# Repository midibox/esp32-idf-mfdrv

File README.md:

# MBHP_MF_NG for ESP32

## Introduction

This application is originated from the PIC based MBHP_MF_NG project: http://www.ucapps.de/mbhp_mf_ng.html

Currently used as a "Proof of Concept" for ESP32 based motorfader control.

Advantage: due to the dedicated PWM outputs of ESP32 we get much more accurate control over the motors.

More documentation to follow...

## Important

Please optimize the app configuration with "idf.py menuconfig":

* Compiler Options->Optimization Level: set to -Os (Release)
* Component Config->ESP32 Specific: set Minimum Supported ESP32 Revision to 1 (if you have a newer device...)
* Component Config->ESP32 Specific: set CPU frequency to 240 MHz
* Component Config->FreeRTOS: set Tick rate (Hz) to 1000

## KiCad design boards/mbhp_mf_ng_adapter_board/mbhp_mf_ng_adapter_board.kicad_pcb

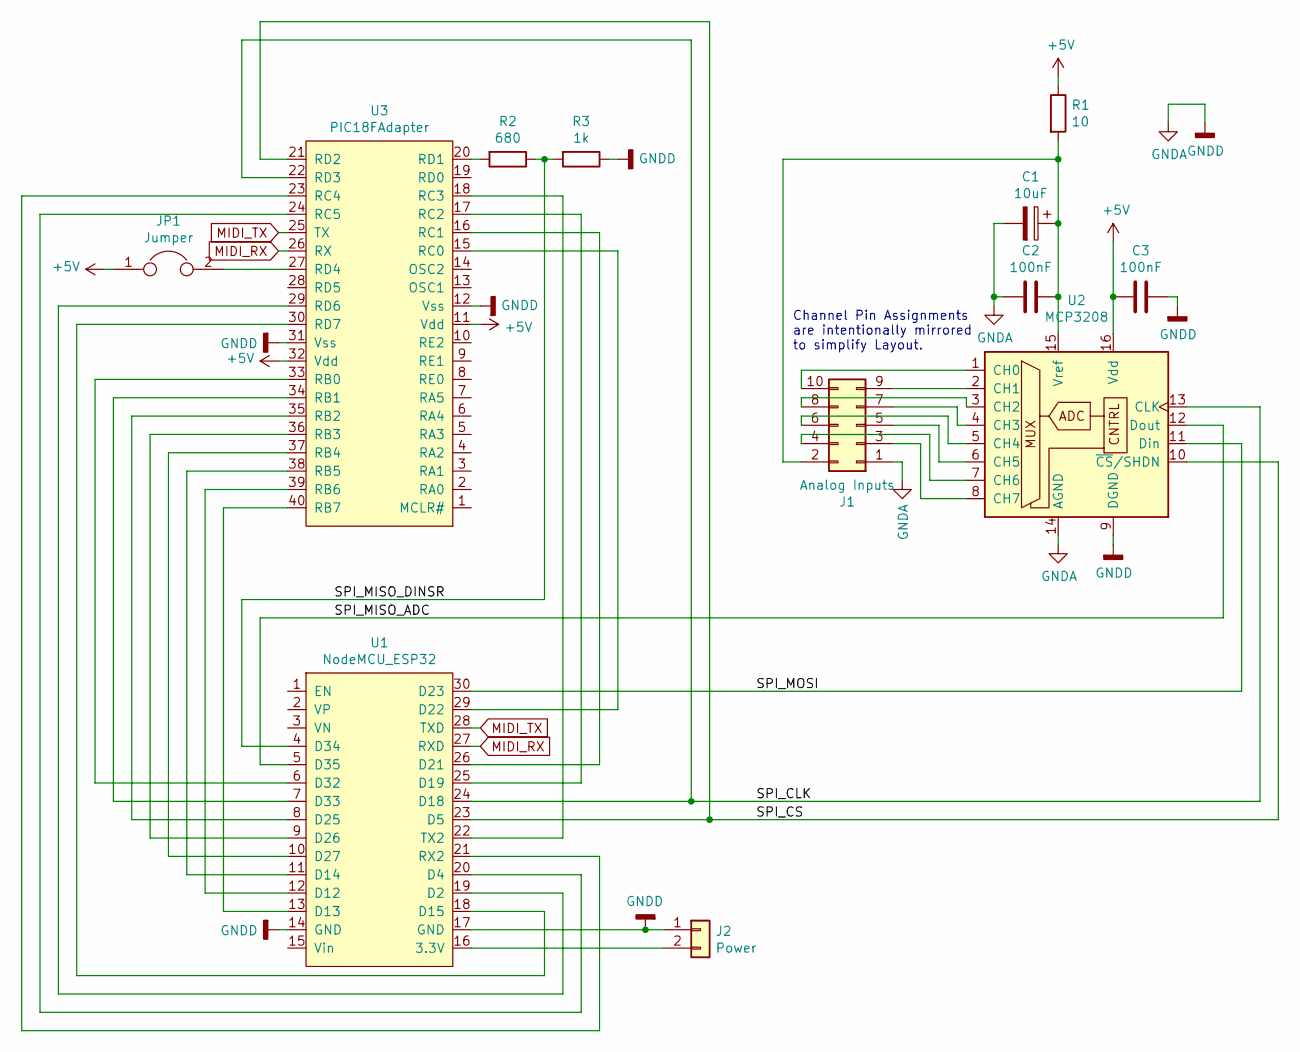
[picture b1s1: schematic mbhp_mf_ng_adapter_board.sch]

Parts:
C1: 10uF; CP_Radial_D5.0mm_P2.50mm
C2, C3: 100nF; C_Rect_L4.6mm_W2.0mm_P2.50mm_MKS02_FKP02
J1: Analog Inputs; IDC-Header_2x05_P2.54mm_Vertical
J2: Power; PinHeader_1x02_P2.54mm_Vertical
JP1: Jumper; PinHeader_1x02_P2.54mm_Vertical
R1: 10; R_Axial_DIN0207_L6.3mm_D2.5mm_P7.62mm_Horizontal
R2: 680; R_Axial_DIN0207_L6.3mm_D2.5mm_P7.62mm_Horizontal
R3: 1k; R_Axial_DIN0207_L6.3mm_D2.5mm_P7.62mm_Horizontal
U1: NodeMCU_ESP32; NodeMCUESP32
U2: MCP3208; DIP-16_W7.62mm_Socket
U3: PIC18FAdapter; DIP40HookUp

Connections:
+5V: C3.2, JP1.1, R1.1, U2.16 (Vdd), U3.11 (Vdd), U3.32 (Vdd)
/SPI_CLK: U1.24 (D18), U2.13 (CLK), U3.22 (RD3)
/SPI_CS: U1.23 (D5), U2.10 (~CS~/SHDN), U3.21 (RD2)
/SPI_MISO_ADC: U1.5 (D35), U2.12 (Dout)
/SPI_MISO_DINSR: R2.1, R3.2, U1.4 (D34)
/SPI_MOSI: U1.30 (D23), U2.11 (Din)
GNDA: C1.2, C2.2, C3.1, J1.1, J2.1, R3.1, U1.14 (GND), U1.17 (GND), U2.9 (DGND), U2.14 (AGND), U3.12 (Vss), U3.31 (Vss)
MIDI_RX: U1.27 (RXD), U3.26 (RX)
MIDI_TX: U1.28 (TXD), U3.25 (TX)
unnamed: C1.1, C2.1, J1.2, R1.2, U2.15 (Vref)
unnamed: J1.3, U2.8 (CH7)
unnamed: J1.4, U2.7 (CH6)
unnamed: J1.5, U2.6 (CH5)
unnamed: J1.6, U2.5 (CH4)
unnamed: J1.7, U2.4 (CH3)
unnamed: J1.8, U2.3 (CH2)
unnamed: J1.9, U2.2 (CH1)
unnamed: J1.10, U2.1 (CH0)
unnamed: J2.2, U1.16 (3.3V)
unnamed: JP1.2, U3.27 (RD4)
unnamed: R2.2, U3.20 (RD1)
unnamed: U1.6 (D32), U3.33 (RB0)
unnamed: U1.7 (D33), U3.34 (RB1)
unnamed: U1.8 (D25), U3.35 (RB2)
unnamed: U1.9 (D26), U3.36 (RB3)
unnamed: U1.10 (D27), U3.37 (RB4)
unnamed: U1.11 (D14), U3.38 (RB5)
unnamed: U1.12 (D12), U3.39 (RB6)
unnamed: U1.13 (D13), U3.40 (RB7)
unnamed: U1.18 (D15), U3.30 (RD7)
unnamed: U1.19 (D2), U3.29 (RD6)
unnamed: U1.20 (D4), U3.24 (RC5)
unnamed: U1.21 (RX2), U3.23 (RC4)
unnamed: U1.22 (TX2), U3.18 (RC3)
unnamed: U1.25 (D19), U3.17 (RC2)
unnamed: U1.26 (D21), U3.16 (RC1)
unnamed: U1.29 (D22), U3.15 (RC0)

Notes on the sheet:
Channel Pin Assignments are intentionally mirrored to simplify Layout.

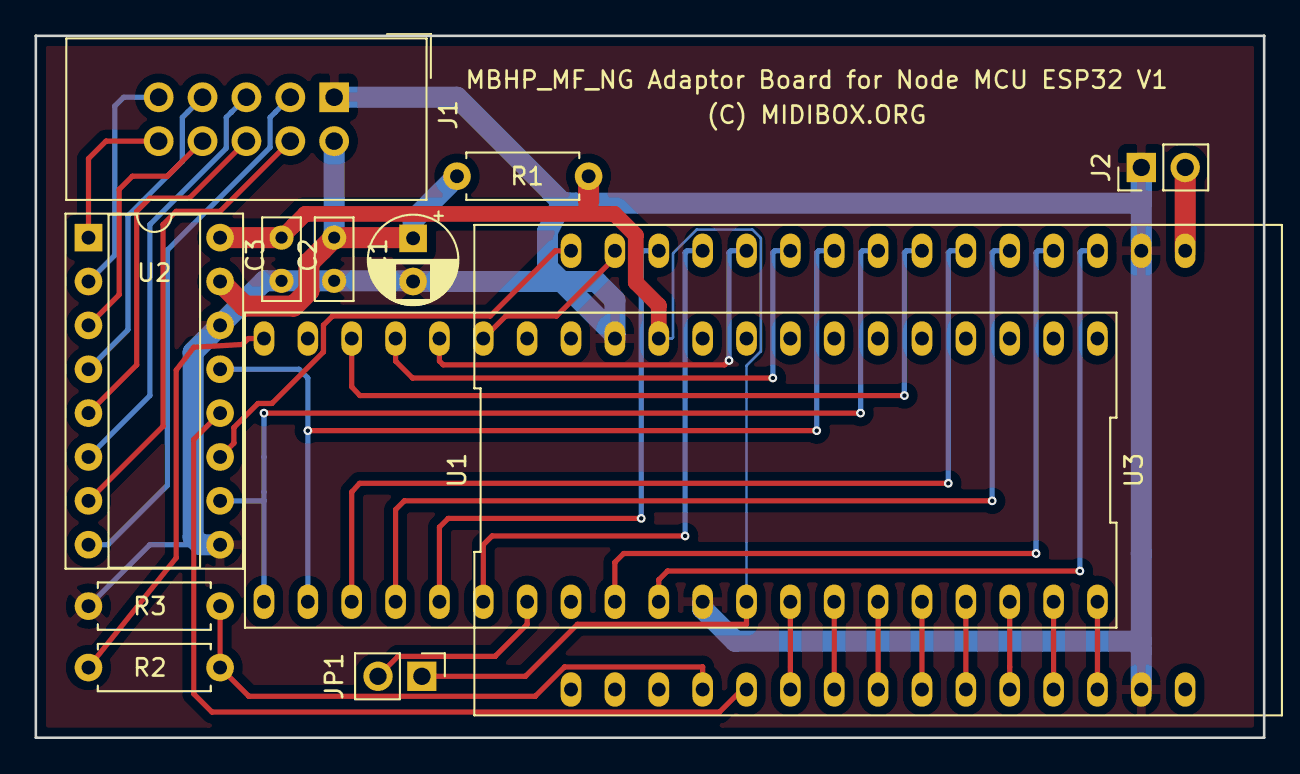
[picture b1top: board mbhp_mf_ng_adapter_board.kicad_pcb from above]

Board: 2 copper layers, 71.1 x 40.6 mm, 12 parts (0 on the bottom side), 37 nets.

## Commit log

2019-12-18 blemidi update
2019-12-19 support for incoming continued SysEx stream
2019-12-21 initial version of MBHP_MF_NG adaptor board
2019-12-22 Adaptor prototype ready for OSHpark
2020-01-02 blemidi driver updates
2020-01-04 added support for Apple MIDI protocol via WIFI
2020-01-05 harmonized BLEMIDI API with Apple MIDI driver
2020-01-05 added sdkconfig.defaults and partition table
2020-01-06 integrated UART MIDI
2020-01-26 allow to enable UART0 MIDI via Jumper (e.g. at Pin 36)
